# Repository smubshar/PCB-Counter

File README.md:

# PCB-Counter
Count items in close range (0.2 - 15mm) using tcrt5000l sensor.

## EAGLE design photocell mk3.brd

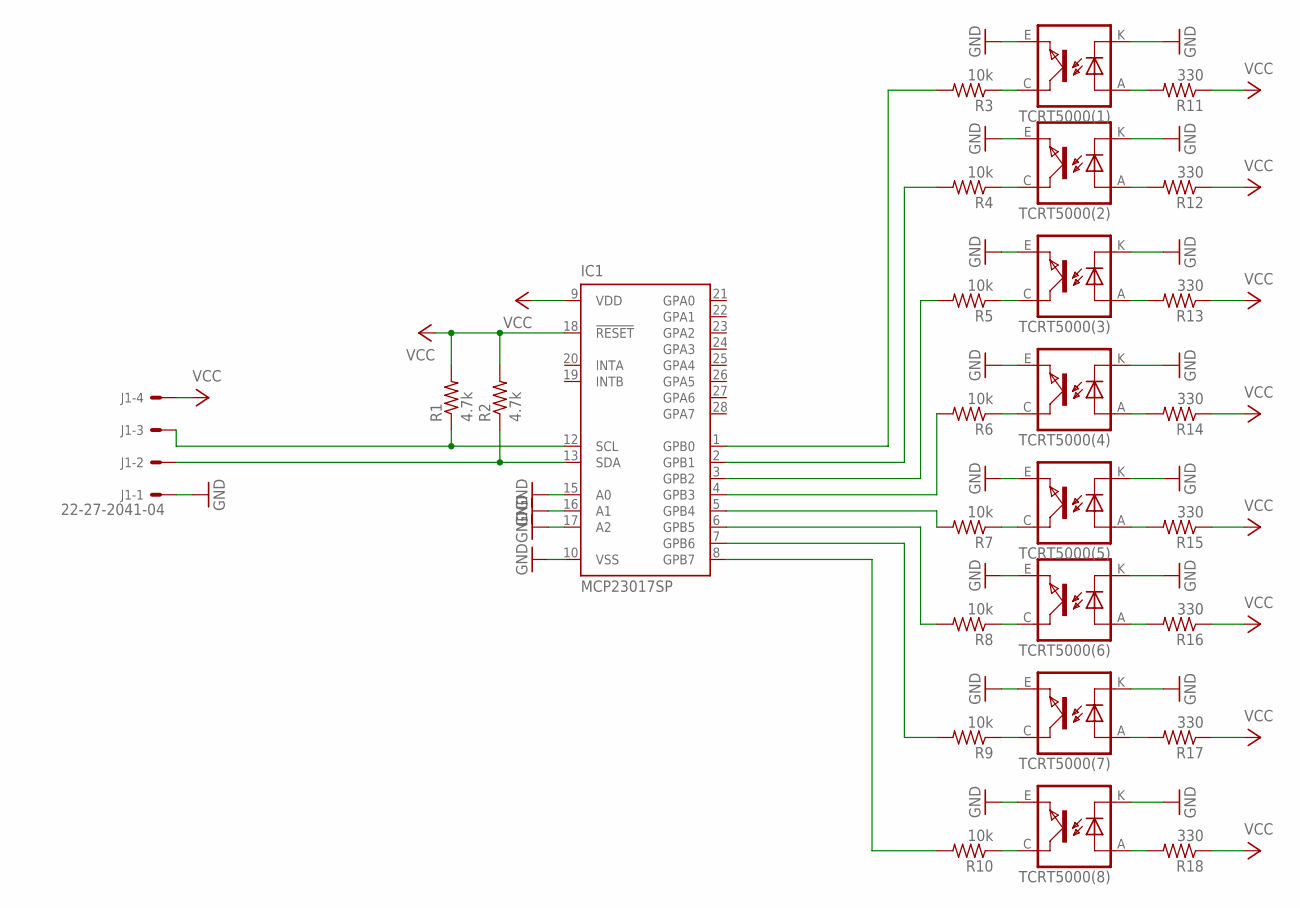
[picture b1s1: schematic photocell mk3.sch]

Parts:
IC1: MCP23017SP; DIL28-3
J1: 22-27-2041-04; 6410-04
R1, R2: 4.7k; 0204/7
R3, R4, R5, R6, R7, R8, R9, R10: 10k; 0204/7
R11, R12, R13, R14, R15, R16, R17, R18: 330; 0204/7
TCRT5000(1), TCRT5000(2), TCRT5000(3), TCRT5000(4), TCRT5000(5), TCRT5000(6), TCRT5000(7), TCRT5000(8): TCRT5000

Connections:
GND: IC1.10 (VSS), IC1.15 (A0), IC1.16 (A1), IC1.17 (A2), J1.1, TCRT5000(1).E (EMITTER), TCRT5000(1).K (CATHODE), TCRT5000(2).E (EMITTER), TCRT5000(2).K (CATHODE), TCRT5000(3).E (EMITTER), TCRT5000(3).K (CATHODE), TCRT5000(4).E (EMITTER), TCRT5000(4).K (CATHODE), TCRT5000(5).E (EMITTER), TCRT5000(5).K (CATHODE), TCRT5000(6).E (EMITTER), TCRT5000(6).K (CATHODE), TCRT5000(7).E (EMITTER), TCRT5000(7).K (CATHODE), TCRT5000(8).E (EMITTER), TCRT5000(8).K (CATHODE)
unnamed: IC1.6 (GPB5), R8.2
unnamed: R18.2, TCRT5000(8).A (ANODE)
unnamed: R10.1, TCRT5000(8).C (COLLECTOR)
unnamed: R9.1, TCRT5000(7).C (COLLECTOR)
unnamed: IC1.7 (GPB6), R9.2
unnamed: R17.2, TCRT5000(7).A (ANODE)
unnamed: IC1.8 (GPB7), R10.2
unnamed: R8.1, TCRT5000(6).C (COLLECTOR)
unnamed: IC1.5 (GPB4), R7.2
unnamed: IC1.4 (GPB3), R6.2
unnamed: R16.2, TCRT5000(6).A (ANODE)
unnamed: IC1.3 (GPB2), R5.2
unnamed: R7.1, TCRT5000(5).C (COLLECTOR)
unnamed: IC1.2 (GPB1), R4.2
unnamed: IC1.1 (GPB0), R3.2
unnamed: IC1.12 (SCL), J1.3, R1.1
unnamed: IC1.13 (SDA), J1.2, R2.1
unnamed: R6.1, TCRT5000(4).C (COLLECTOR)
unnamed: R14.2, TCRT5000(4).A (ANODE)
unnamed: R5.1, TCRT5000(3).C (COLLECTOR)
unnamed: R13.2, TCRT5000(3).A (ANODE)
unnamed: R4.1, TCRT5000(2).C (COLLECTOR)
unnamed: R12.2, TCRT5000(2).A (ANODE)
unnamed: R3.1, TCRT5000(1).C (COLLECTOR)
unnamed: R11.2, TCRT5000(1).A (ANODE)
TCRT5000(5): R15.2, TCRT5000(5).A (ANODE)
VCC: IC1.9 (VDD), IC1.18 (!RESET), J1.4, R1.2, R2.2, R11.1, R12.1, R13.1, R14.1, R15.1, R16.1, R17.1, R18.1

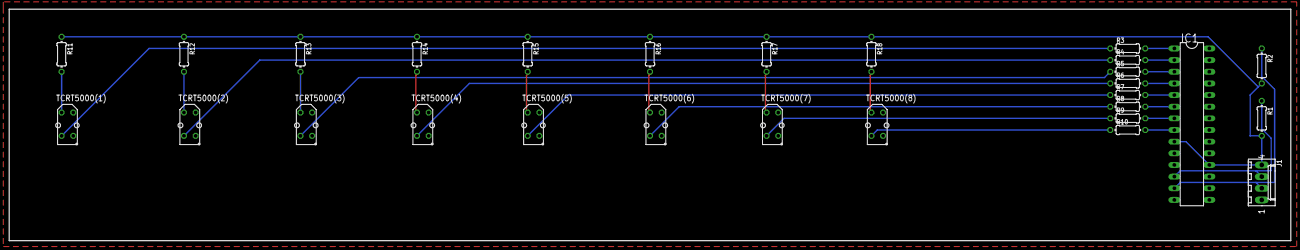
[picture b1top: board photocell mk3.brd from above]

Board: 2 copper layers, 279.4 x 50.5 mm, 28 parts (0 on the bottom side), 28 nets.
